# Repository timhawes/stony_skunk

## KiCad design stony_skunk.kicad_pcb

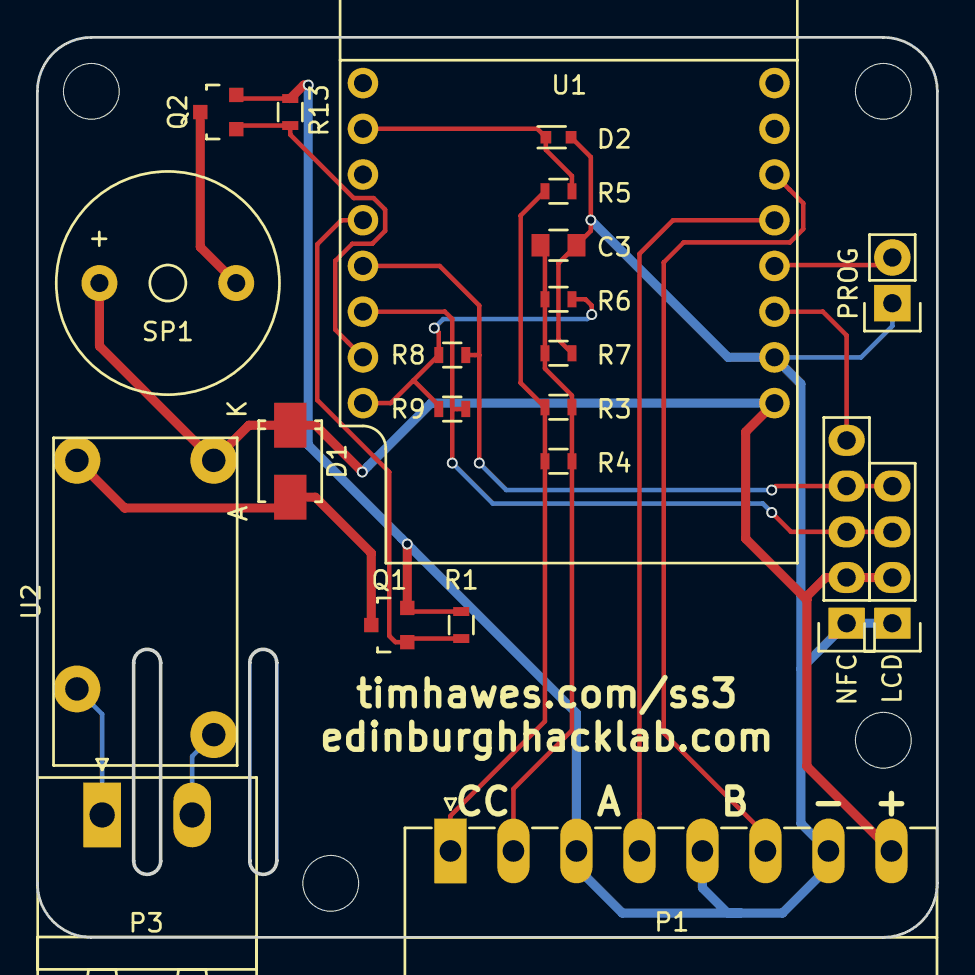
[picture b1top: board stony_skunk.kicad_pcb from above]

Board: 2 copper layers, 50.0 x 50.0 mm, 22 parts (0 on the bottom side), 18 nets.

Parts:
C3: 10uF; C_0805
D1: D; SMA_Standard
D2: ESD5Z3.3T1G; SOD-523
P1: DC/BUTTONS/CURRENT; PhoenixContact_MC-G_08x3.50mm_Angled
P2: LCD; Pin_Header_Straight_1x04
P3: RELAY; PhoenixContact_MSTBA-G_02x5.00mm_Angled
P4: NFC; Pin_Header_Straight_1x05
P7: PROG; Pin_Header_Straight_1x02
Q1, Q2: Q_NMOS_GSD; SOT-23
R1, R6, R7, R13: 10K; R_0603
R3, R4: 200R; R_0603
R5: 1K; R_0603
R8, R9: 2K2; R_0603
SP1: SPEAKER; Buzzer_12x9.5RM7.6
U1: WEMOS_D1_MINI
U2: RELAY; TE_OJ_RELAY

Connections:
+3V3: R6.1, R8.1, R9.1, U1.8
+5V: D1.1, P1.8, P2.2, P4.2, SP1.1, U1.9, U2.1
ADC: D2.1, R5.1, U1.2
BUTTON_A: P1.4, U1.13
BUTTON_B: P1.6, U1.14
BUZZER: Q2.1, R13.1, U1.7
CURRENT_A: P1.1, R3.1, R4.1, R5.2
CURRENT_B: C3.1, P1.2, R3.2, R4.2, R6.2, R7.1
GND: C3.2, D2.2, P1.3, P1.5, P1.7, P2.1, P4.1, P7.1, Q1.2, Q2.2, R1.2, R7.2, R13.2, U1.10
GPIO0: P7.2, U1.12
unnamed: D1.2, Q1.3, U2.2
unnamed: P3.1, U2.3
unnamed: P3.2, U2.4
unnamed: Q2.3, SP1.2
PN532_RESET: P4.5, U1.11
RELAY: Q1.1, R1.1, U1.4
SCL: P2.4, P4.4, R8.2, U1.5
SDA: P2.3, P4.3, R9.2, U1.6

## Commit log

2016-12-07 Flip relay to correct orientation
2017-06-17 Clarified adjustable/optional resistors on schematic
2018-04-04 Replace ESP12E with Wemos D1 Mini
2018-11-07 Convert to Kicad v5 and fix mismatched reference in schematic (R2->R13)
